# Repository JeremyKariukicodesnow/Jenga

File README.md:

# Jenga

**An open-source electronics workspace for people and external AI assistants.**

Jenga brings schematic editing, PCB layout, footprint and symbol libraries, and 3D assemblies into a Rust desktop application. Use the interface yourself, or connect an assistant through deterministic MCP, CLI and JSON tools. Jenga does not include a chat model, require an AI subscription, or make engineering decisions on its own.

Created and maintained by **Jeremy ([@JeremyKariukicodesnow](https://github.com/JeremyKariukicodesnow))**, with development assistance from **ChatGPT / OpenAI Codex**. This is an independent project, not an official KiCad or OpenAI product. The header is an AI-generated conceptual illustration, not an application screenshot.

## Status and downloads

**0.8.1 is early-access software for Windows x64.** It is suitable for evaluation and contributions; it is not a guarantee of production-ready PCB designs. Save backups, inspect exports and run native ERC/DRC before relying on a design. Electrical, thermal, mechanical and bench validation remain the designer's responsibility.

[Download latest Windows installer](https://jenga.sparkfield.co.ke/download/?start=1) · [Older versions / all releases](https://github.com/JeremyKariukicodesnow/Jenga/releases) · [0.8.1 early-access release](https://github.com/JeremyKariukicodesnow/Jenga/releases/tag/v0.8.1) · [User guide](docs/USER_GUIDE.md) · [PCB guide](docs/PCB_GUIDE.md) · [Validation evidence and limits](docs/RELEASE_080_VALIDATION.md)

**One permanent download link:** https://jenga.sparkfield.co.ke/download/?start=1 selects the highest published version, including early-access builds, and starts its EXE download. The public 0.8.1 early-access EXE is available now. [Older versions](https://github.com/JeremyKariukicodesnow/Jenga/releases) remain available separately; new releases never replace their original assets.

**Direct 0.8.1 downloads:**

- [Windows installer (.exe)](https://github.com/JeremyKariukicodesnow/Jenga/releases/download/v0.8.1/Jenga-windows-x64-Setup.exe)
- [Matching original source and Rust dependency source](https://github.com/JeremyKariukicodesnow/Jenga/releases/download/v0.8.1/Jenga-0.8.1-source.zip)
- [Checksums](https://github.com/JeremyKariukicodesnow/Jenga/releases/download/v0.8.1/SHA256SUMS)

Use the permanent download-page link for the newest published build, including previews. The version-specific links above keep the original 0.8.0 files. GitHub's `/latest` endpoint excludes prereleases; the [sharing/video guide](docs/SHARING_AND_VIDEOS.md) explains website buttons and future stable-release links. No demo video is uploaded yet.

The local build produces an installer, portable ZIP, corresponding Jenga/Rust dependency source ZIP and SHA-256 checksums. **The public [0.8.0 early-access release](https://github.com/JeremyKariukicodesnow/Jenga/releases/tag/v0.8.0) includes its installer, matching original source, checksums and a native-runtime notice/source supplement.** Published release artifacts are frozen; repository main can contain later dependency/CI/documentation changes. See [publication evidence and future release checks](docs/PUBLIC_RELEASE_CHECKLIST.md). Portable archives are available only where explicitly attached to a release. Do not use a source snapshot as an installer or treat an unlisted third-party download as an official build.

The complete Windows package includes symbols, footprints, 3D library data and the native KiCad backend; a separate KiCad installation is not required. This makes the offline package relatively large. Windows binaries are currently unsigned; there is no automatic online updater or established security audit.

## Why Jenga?

Jenga aims to make an electronics task useful in one workspace: draw the circuit, inspect connectivity, make a board, preview the assembly and export the result. For assistants, the same project has explicit tool targets, operation IDs and reviewable changes, reducing fragile screen-clicking and custom Python orchestration. People can still work directly in the desktop interface.

The stable connection bridge addresses a common interruption: after an app upgrade/downgrade, the assistant should recover its worker without the user repeatedly saying “reconnect.” Revision checks and previews protect human edits; they do not guarantee that an AI's electrical choices are correct.

It is a promising, useful prototype with substantial implemented workflows. **It is not perfect:** complex routing, advanced KiCad interoperability, engineering review and clean-machine coverage still need work. More generated tracks or an attractive 3D image do not prove a design is ready to manufacture.

## Requirements

| Requirement | Current position |
| --- | --- |
| Operating system | Windows x64 binary release; Windows 10/11 are the intended desktop targets. Broader clean-machine and driver coverage remains pending. No validated Linux/macOS binary releases yet. |
| Graphics | A working graphics driver for the OpenGL-based desktop renderer. VM/remote-desktop graphics compatibility is not comprehensively tested. |
| Disk | The complete extracted 0.8.0 payload is approximately **4.1 GB**; allow additional space for the download, installer staging, projects and exports. This is a measured payload size, not a universal minimum free-space guarantee. |
| Memory | Depends on board complexity and model size. No verified minimum-RAM figure or controlled performance benchmark is published yet. |
| KiCad | **Not required for the complete Jenga Windows package.** It includes the native backend and symbol, footprint and 3D libraries. A source-only checkout excludes those large binaries/assets and needs preparation steps. |
| AI | Optional. Manual editing requires no AI account or API key. Automation requires a local-capable assistant/client; its own provider/account and network requirements apply. |
| Internet | Not needed for local editing with the complete offline package. Needed for downloads, web asset discovery and any externally hosted assistant that requires it. |

Installing a binary does not require Rust or compiler tools; those are development requirements only. Download all of the portable package, rather than copying just Jenga.exe.

## What you can do

| Area | Available workflows |
| --- | --- |
| Schematics | Place and edit symbols; draw full wires, junctions and labels; manage independent drawings and hierarchical sheets; inspect connections and export drawings. |
| PCB | Create independent boards or optionally link a schematic; place footprints, route copper, manage layers/zones, inspect findings and export manufacturing data. |
| Libraries | Create/edit custom symbols and footprints; attach 3D models; import native assets into a project or personal library. |
| 3D | Inspect the assembly in a tab or separate window, adjust brightness/ambient light, export camera PNG/PDF views and supported CAD model formats. |
| Automation | MCP/CLI/JSON discovery, revision-guarded previews and commits, compact inspection, background calculations, progress/cancellation and durable operation receipts. |
| KiCad exchange | Open modern native projects/files; import projects or independent documents; exchange supported clipboard objects while preserving unknown fields in native files. |

Compatibility is incremental. Legacy `.sch`, every historic KiCad version and every advanced clipboard object are **not** supported. Unsupported clipboard objects are reported rather than silently discarded. Complete hierarchical projects use whole-project import. Jenga's approximate checks do not replace native DRC for complex rules. See the validation report for the precise test boundaries.

## Get started

When a verified binary release becomes available:

1. Download the versioned installer or portable ZIP and its `SHA256SUMS` from this repository's Releases page.
2. Check the downloaded hash, for example `Get-FileHash .\Jenga-0.8.0-windows-x64-Setup.exe -Algorithm SHA256`.
3. Run the installer, or extract the complete portable ZIP and launch `Jenga/Jenga.exe`.
4. Create/open a project, then add a schematic, PCB, or both. Linking a board to a schematic is optional.

For existing installations, Setup offers Upgrade, Repair or Downgrade and preserves project/personal data. Save work before maintenance. Keep a backup before downgrading a project made with newer features.

### Connect an assistant

Use **Connect Assistant** or the installed CLI:

```powershell
jenga-cli setup --client Codex --workspace "$env:USERPROFILE\Documents" --install --skill
```

Setup registers a stable `jenga-connect.exe` bridge outside the replaced application directory. Existing assistants need one restart to adopt it. Later worker upgrades/downgrades reconnect automatically without a new pasted configuration. Hosts that cannot refresh MCP tool lists may still need a restart. Interrupted edits are never replayed blindly: inspect the retained operation ID, then reopen the intended saved document if needed.

**Assistant setup:** built-in registration helpers cover Codex, Claude Code, Cursor and Antigravity. Other local MCP stdio clients can use the generated generic configuration; assistants with local command execution can use the CLI/JSON API. Browser-only chat does not automatically have access to local Jenga files. See [which assistants and setup recipes](docs/AI_ASSISTANTS.md).

The assistant supplies the engineering reasoning. The bundled skill covers exact part/datasheet evidence, power budgets, full visible wiring, readable labels, ground/antenna review and reusing appropriately licensed manufacturer/community assets. See [automation](docs/AUTOMATION.md) and the [skill](docs/assistant-skill/jenga-design/SKILL.md).

## Build from source

Install a current stable Rust toolchain (dependency MSRVs apply), Windows MSVC build tools and Git. The current desktop/release validation target is Windows x64.

```powershell
cargo test --workspace --locked
cargo run -p jenga-desktop
```

The repository includes font source and small fixtures, but deliberately excludes gigabytes of binary libraries, backend binaries, local settings, caches and personal projects. For a complete offline Windows package, obtain official KiCad 10 libraries/backend locally, then run:

```powershell
./scripts/prepare-libraries.ps1 -KiCadRoot 'C:\Program Files\KiCad\10.0'
./scripts/prepare-pcb-backend.ps1 -KiCadRoot 'C:\Program Files\KiCad\10.0'
./scripts/build-release.ps1
```

Inno Setup is needed to create Setup.exe. Audit redistribution notices/source availability before publishing a bundle. A dependency-vendored source archive accompanies binary releases; full offline library assets have separate provenance/licenses.

## Collaborate

Start with [CONTRIBUTING.md](CONTRIBUTING.md), [CODE_OF_CONDUCT.md](CODE_OF_CONDUCT.md) and [GOVERNANCE.md](GOVERNANCE.md). Fork, create a focused branch, add meaningful tests and open a pull request. Public visibility does not grant write or merge access. The maintainer controls upstream membership, merging, tags and releases; branch protection requires review and passing checks.

Report ordinary bugs with a minimal redistributable fixture. **Do not post credentials, personal projects or private security findings in public issues.** Follow [SECURITY.md](SECURITY.md) for vulnerabilities. AI-assisted contributions are welcome when reviewed and tested by the human contributor, with sources and limitations disclosed.

## Versioning and roadmap

`Cargo.toml` is the version source of truth. This release remains **0.8.0**. Tags use `v0.8.0`; release labels distinguish drafts, early-access prereleases and stable releases without silently changing the application's version.

Before 1.0, minor versions may change preview APIs. Existing projects must remain protected by explicit migrations and backups. Patches contain fixes; minors add features; a future 1.0 requires a documented compatibility/support commitment. Never replace published release assets silently. See [CHANGELOG.md](CHANGELOG.md) and [release policy](docs/RELEASING.md).

Next priorities are broader KiCad interoperability fixtures, clean-machine validation, independent engineering review, code signing, third-party distribution completeness and measured performance benchmarks.

## License and acknowledgements

Jenga's code is licensed under **GPL-3.0-or-later**, subject to the separately identified third-party material. Commercial use is allowed under the applicable licenses; this is not a proprietary license or an exclusive ownership claim over upstream work.

Thank you to the **KiCad developers, library contributors, Vladimir Uryvaev and NewStroke contributors**, and the maintainers of Rust dependencies and native runtime dependencies. The NewStroke source is included with its notices; KiCad libraries and backend have their own distribution obligations. See [THIRD_PARTY_NOTICES.md](THIRD_PARTY_NOTICES.md), [AUTHORS.md](AUTHORS.md) and [LICENSE](LICENSE).

No warranty is provided. Jenga is not affiliated with or endorsed by KiCad or OpenAI. Attribution, tests and a license do not substitute for a security audit, license compliance review or hardware validation.

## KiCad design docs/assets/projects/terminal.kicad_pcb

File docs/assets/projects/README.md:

# Project showcase exports

These PNGs are unmodified exports copied from Jeremy's local 555 Pulse Generator, Maize Factory, and Access Terminal S3 projects for the public Jenga showcase. They show design artifacts, not fabricated or certified hardware. The terminal remains subject to engineering review, as described on the website. The Maize Factory project is represented by its power and control schematics only.

The GLB files are actual exported 3D assemblies, not turntable videos. Native schematic and PCB files are offered for inspection. Native boards can reference project-specific external models or libraries; the self-contained GLB is the portable visual assembly. Downloads are development examples, not manufacturing-approved designs.

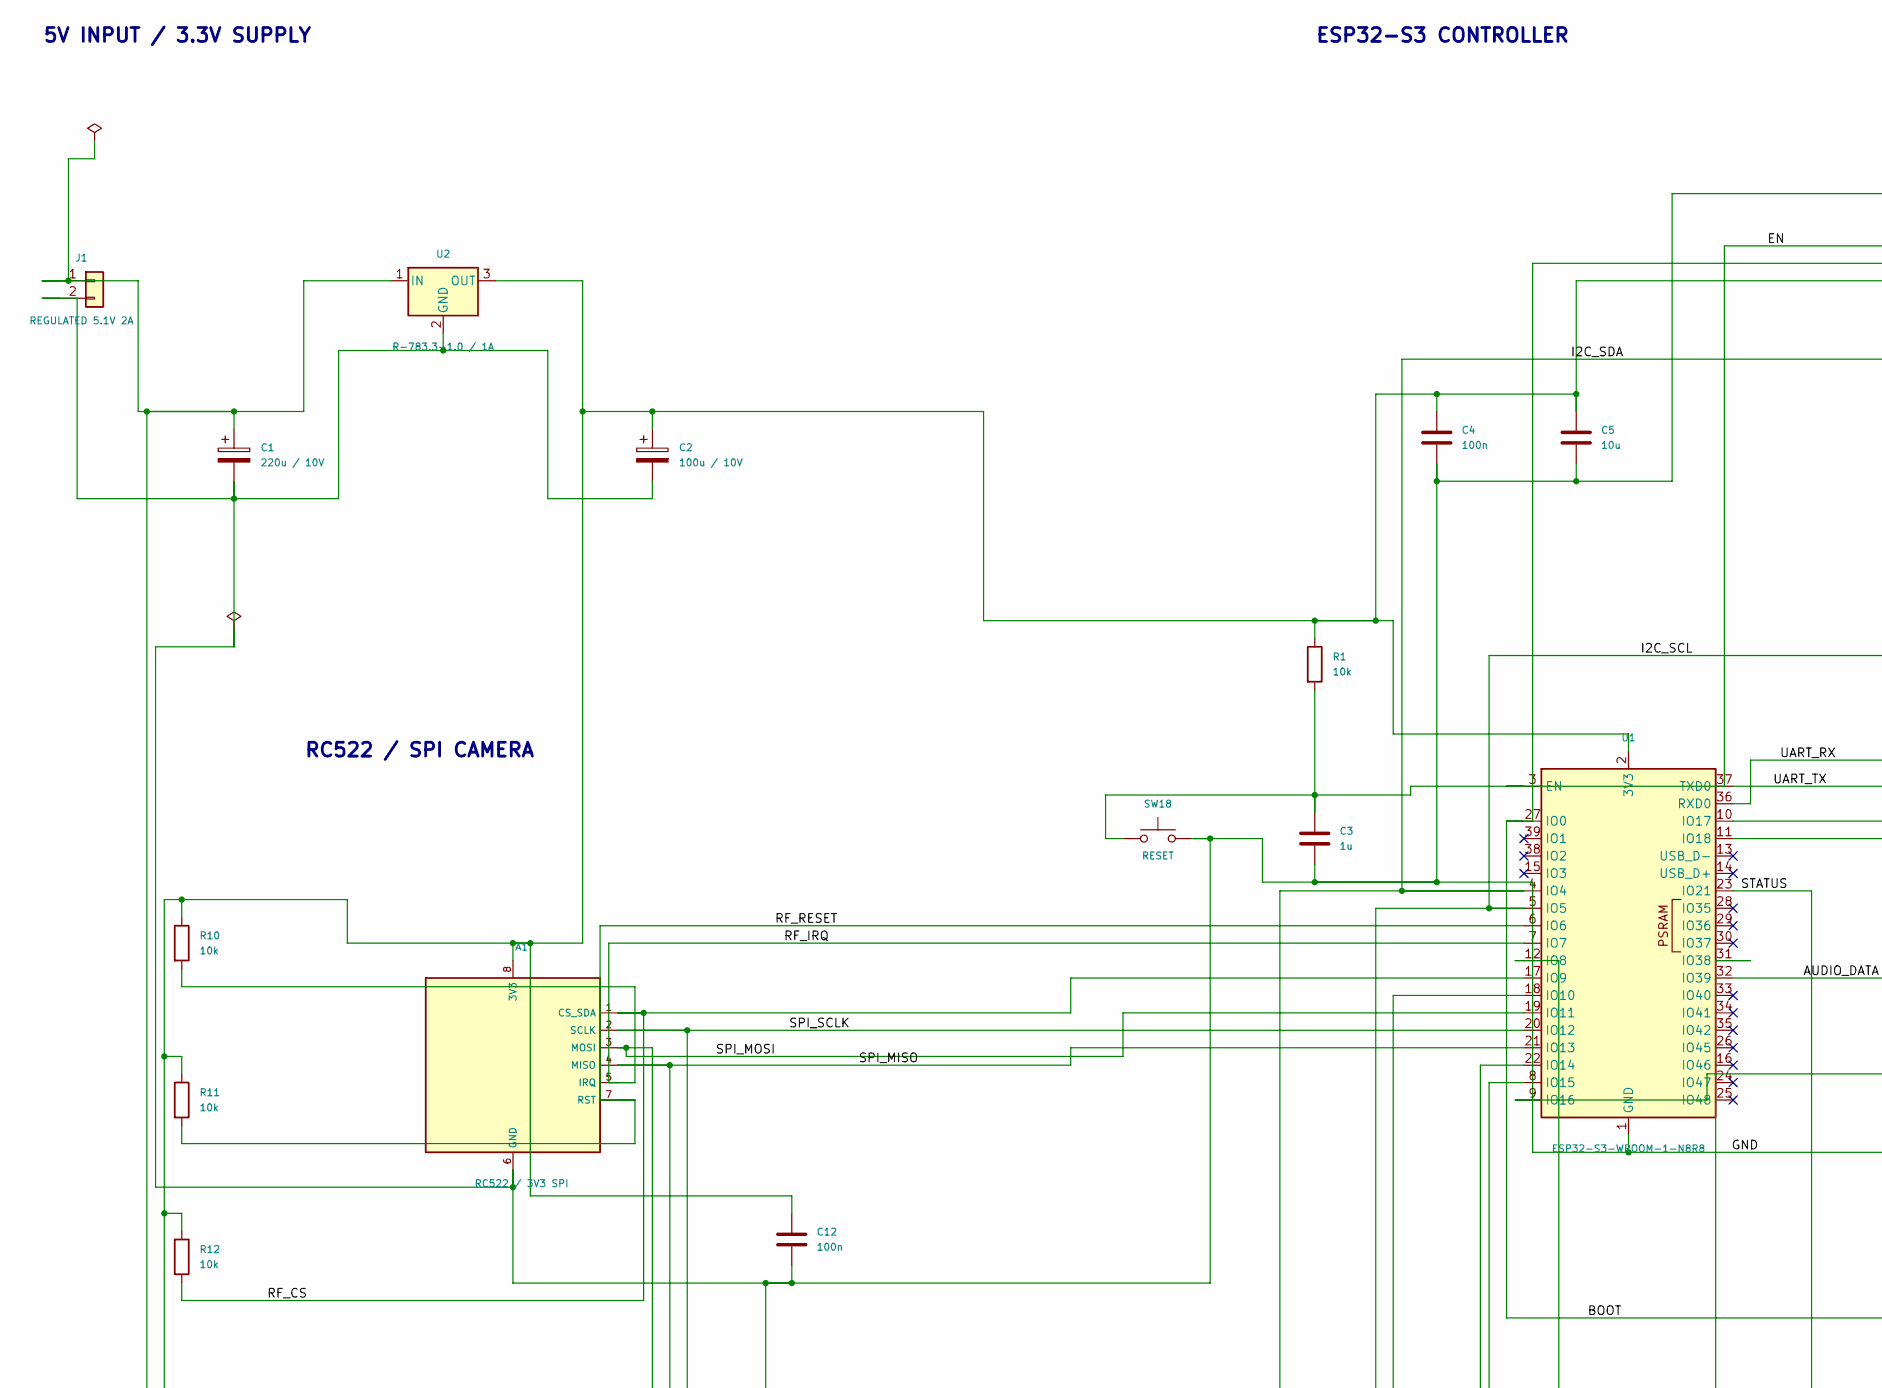
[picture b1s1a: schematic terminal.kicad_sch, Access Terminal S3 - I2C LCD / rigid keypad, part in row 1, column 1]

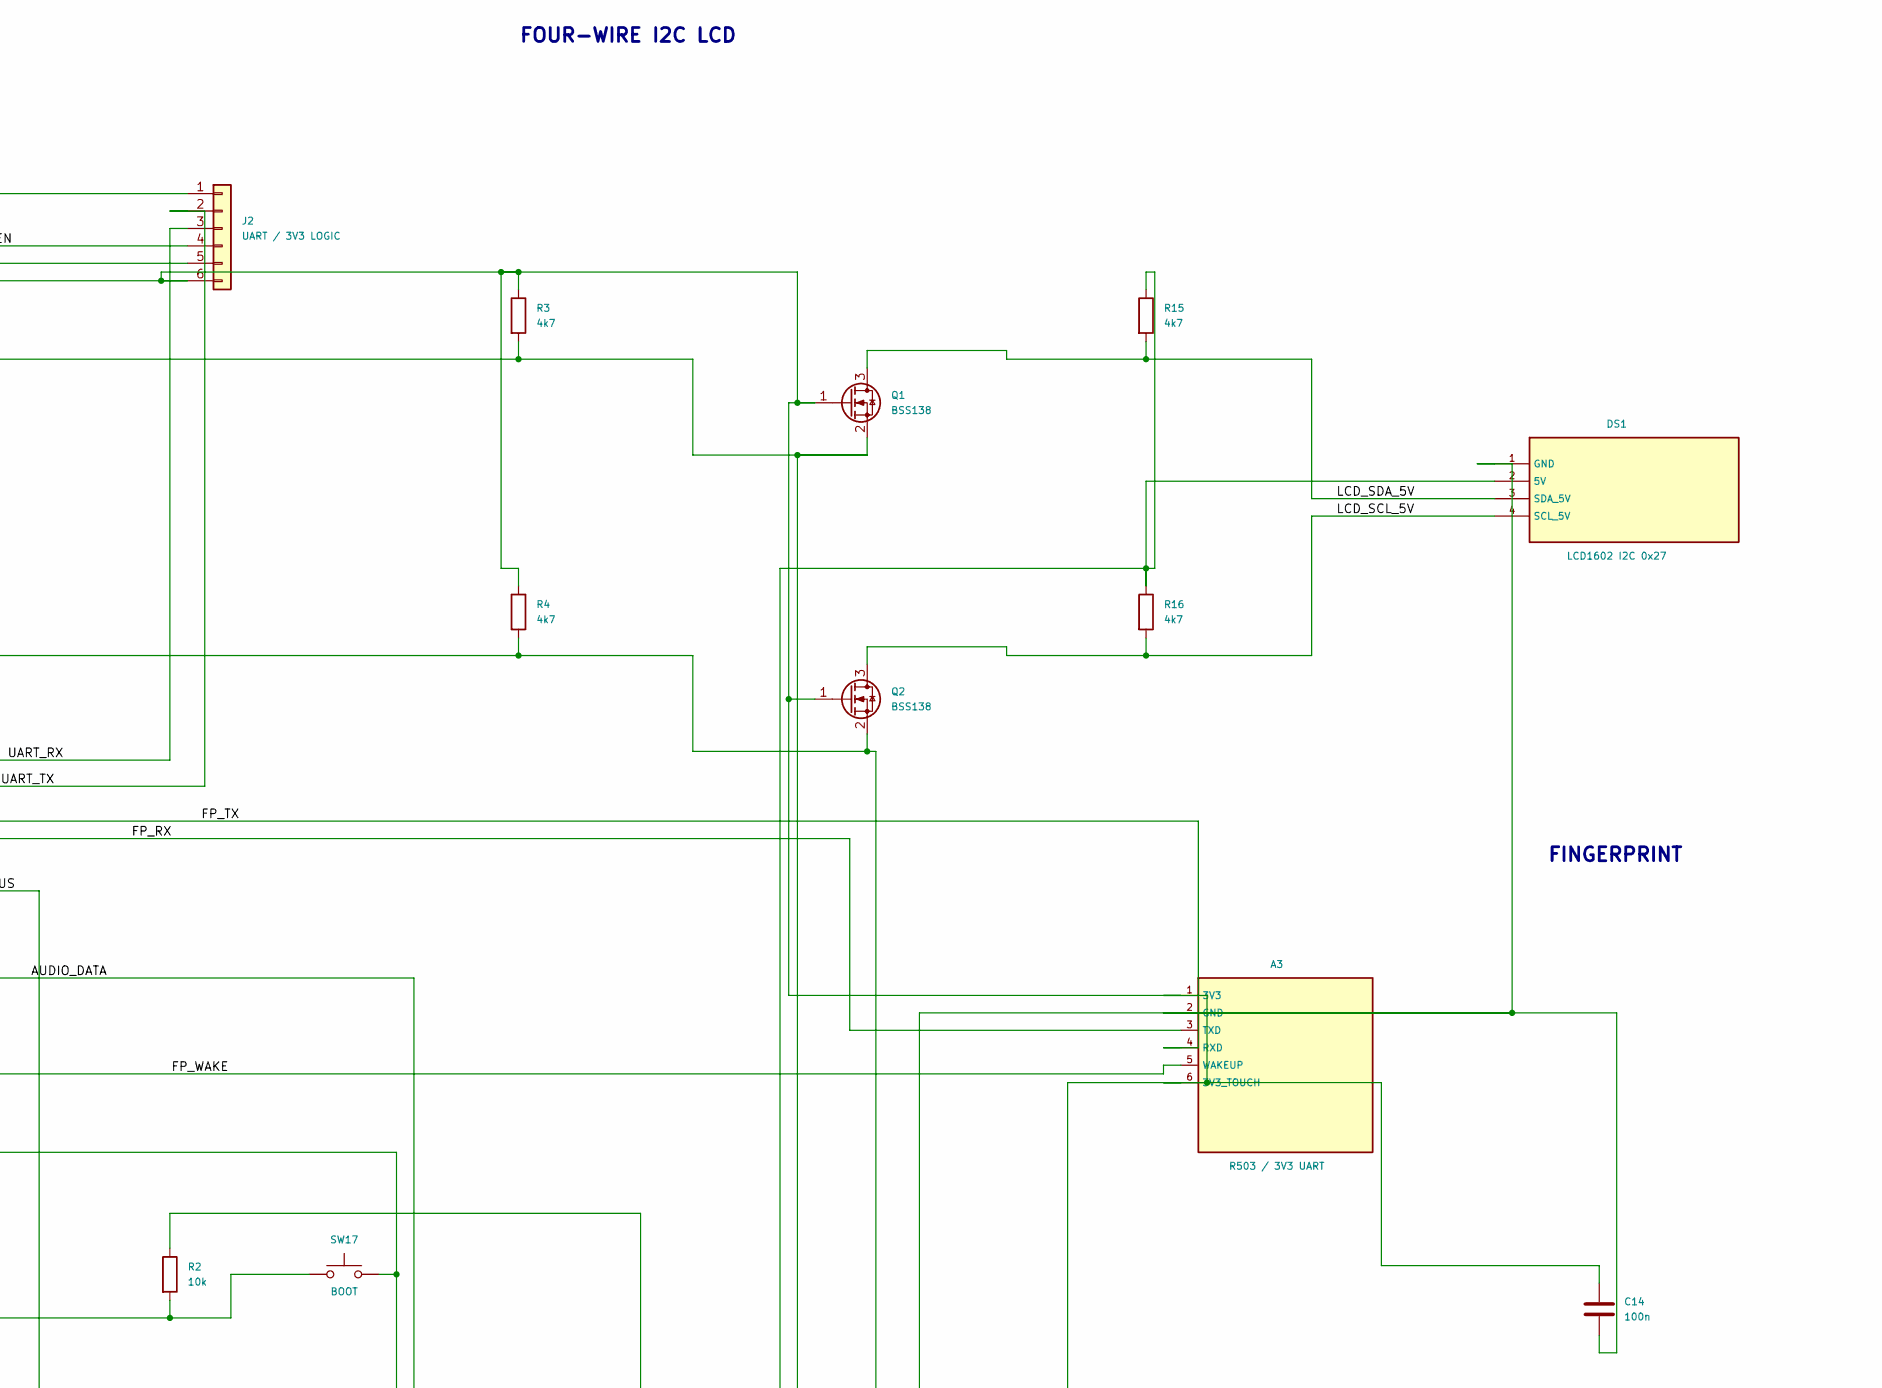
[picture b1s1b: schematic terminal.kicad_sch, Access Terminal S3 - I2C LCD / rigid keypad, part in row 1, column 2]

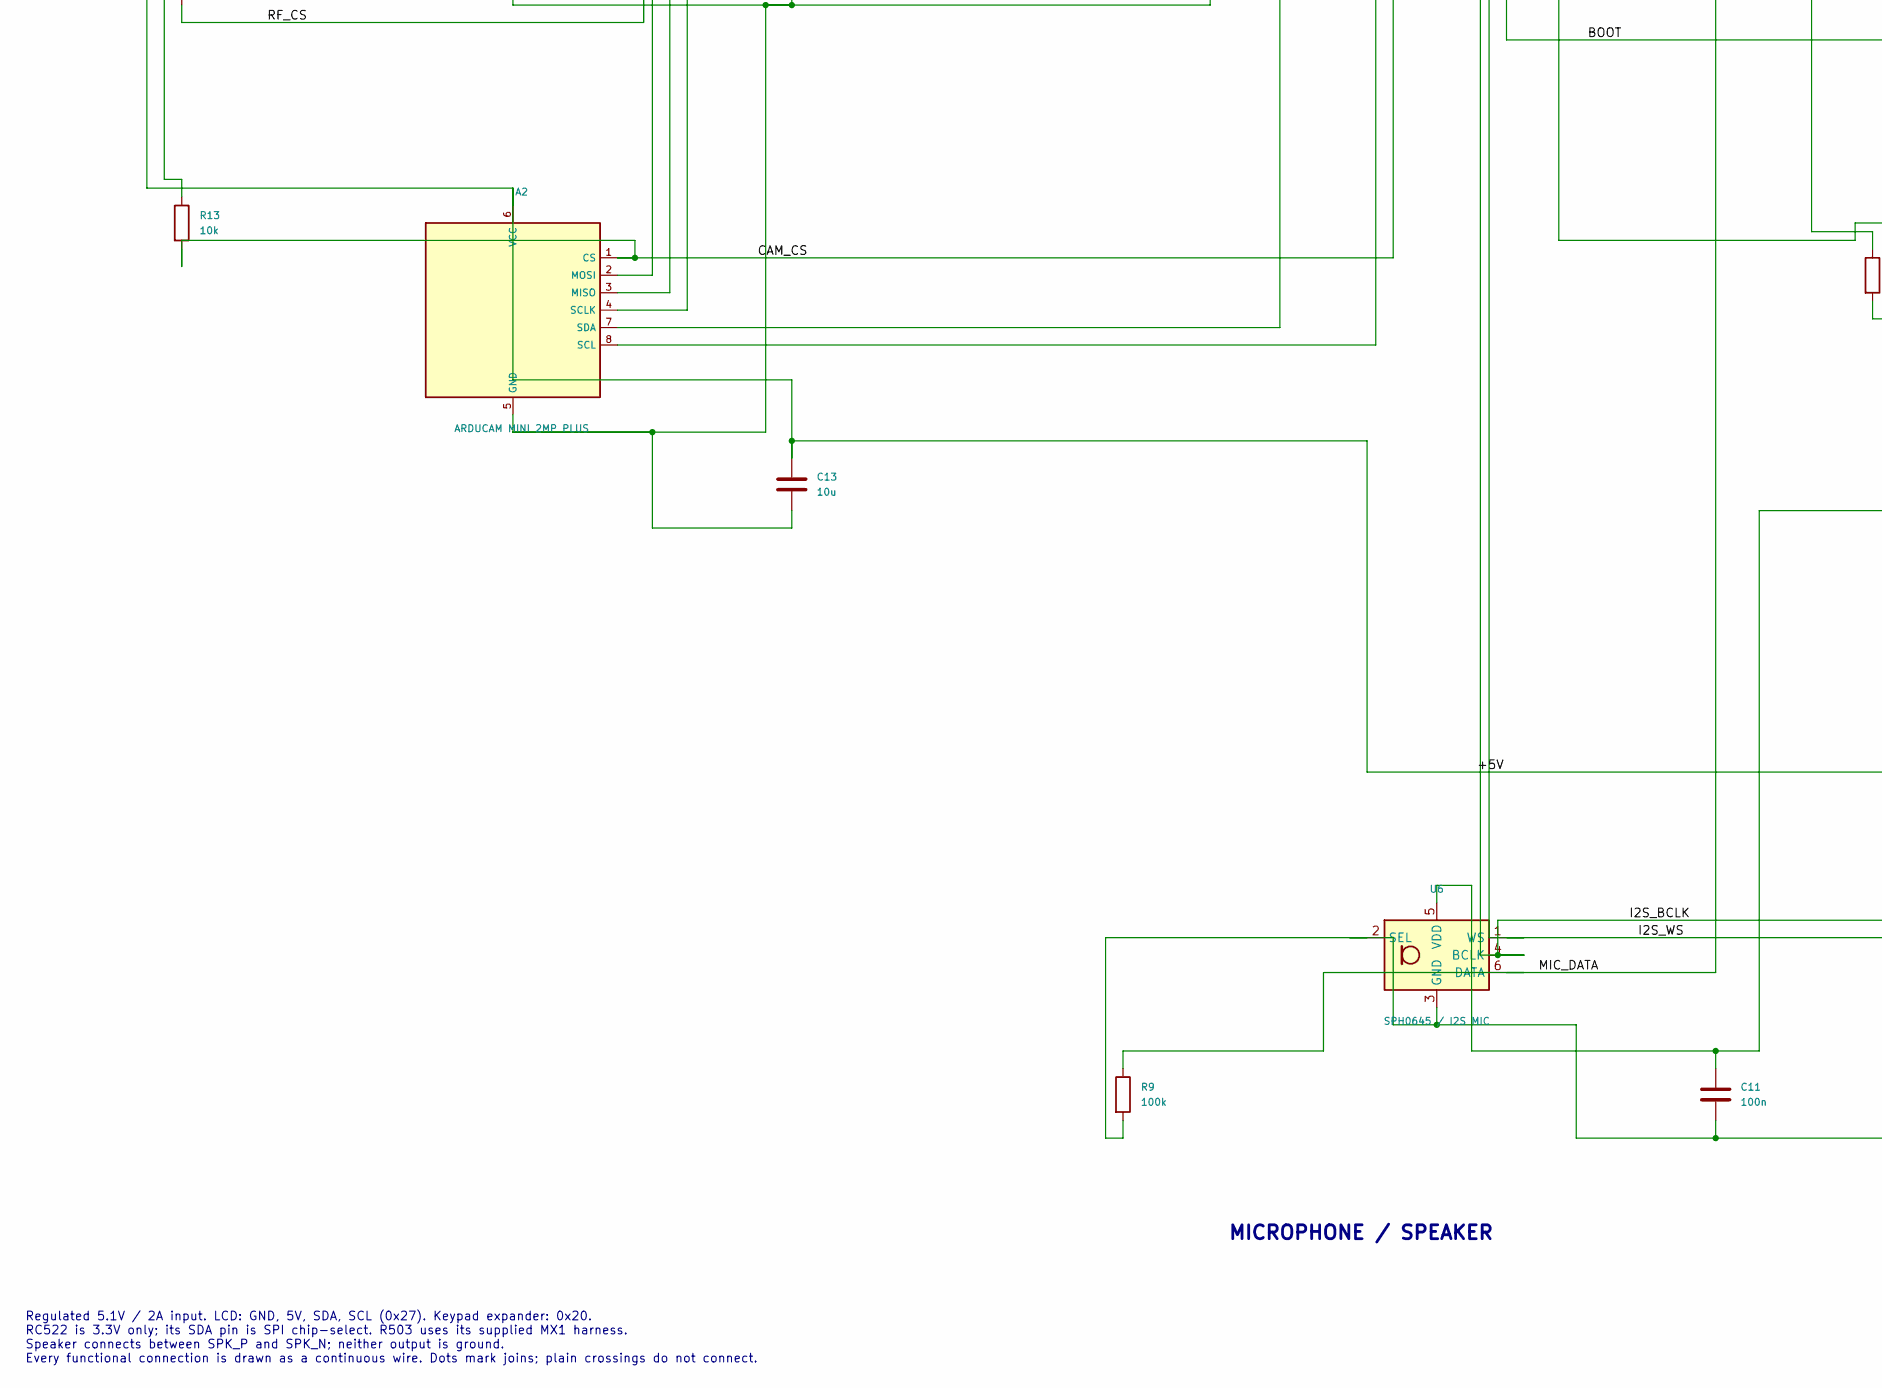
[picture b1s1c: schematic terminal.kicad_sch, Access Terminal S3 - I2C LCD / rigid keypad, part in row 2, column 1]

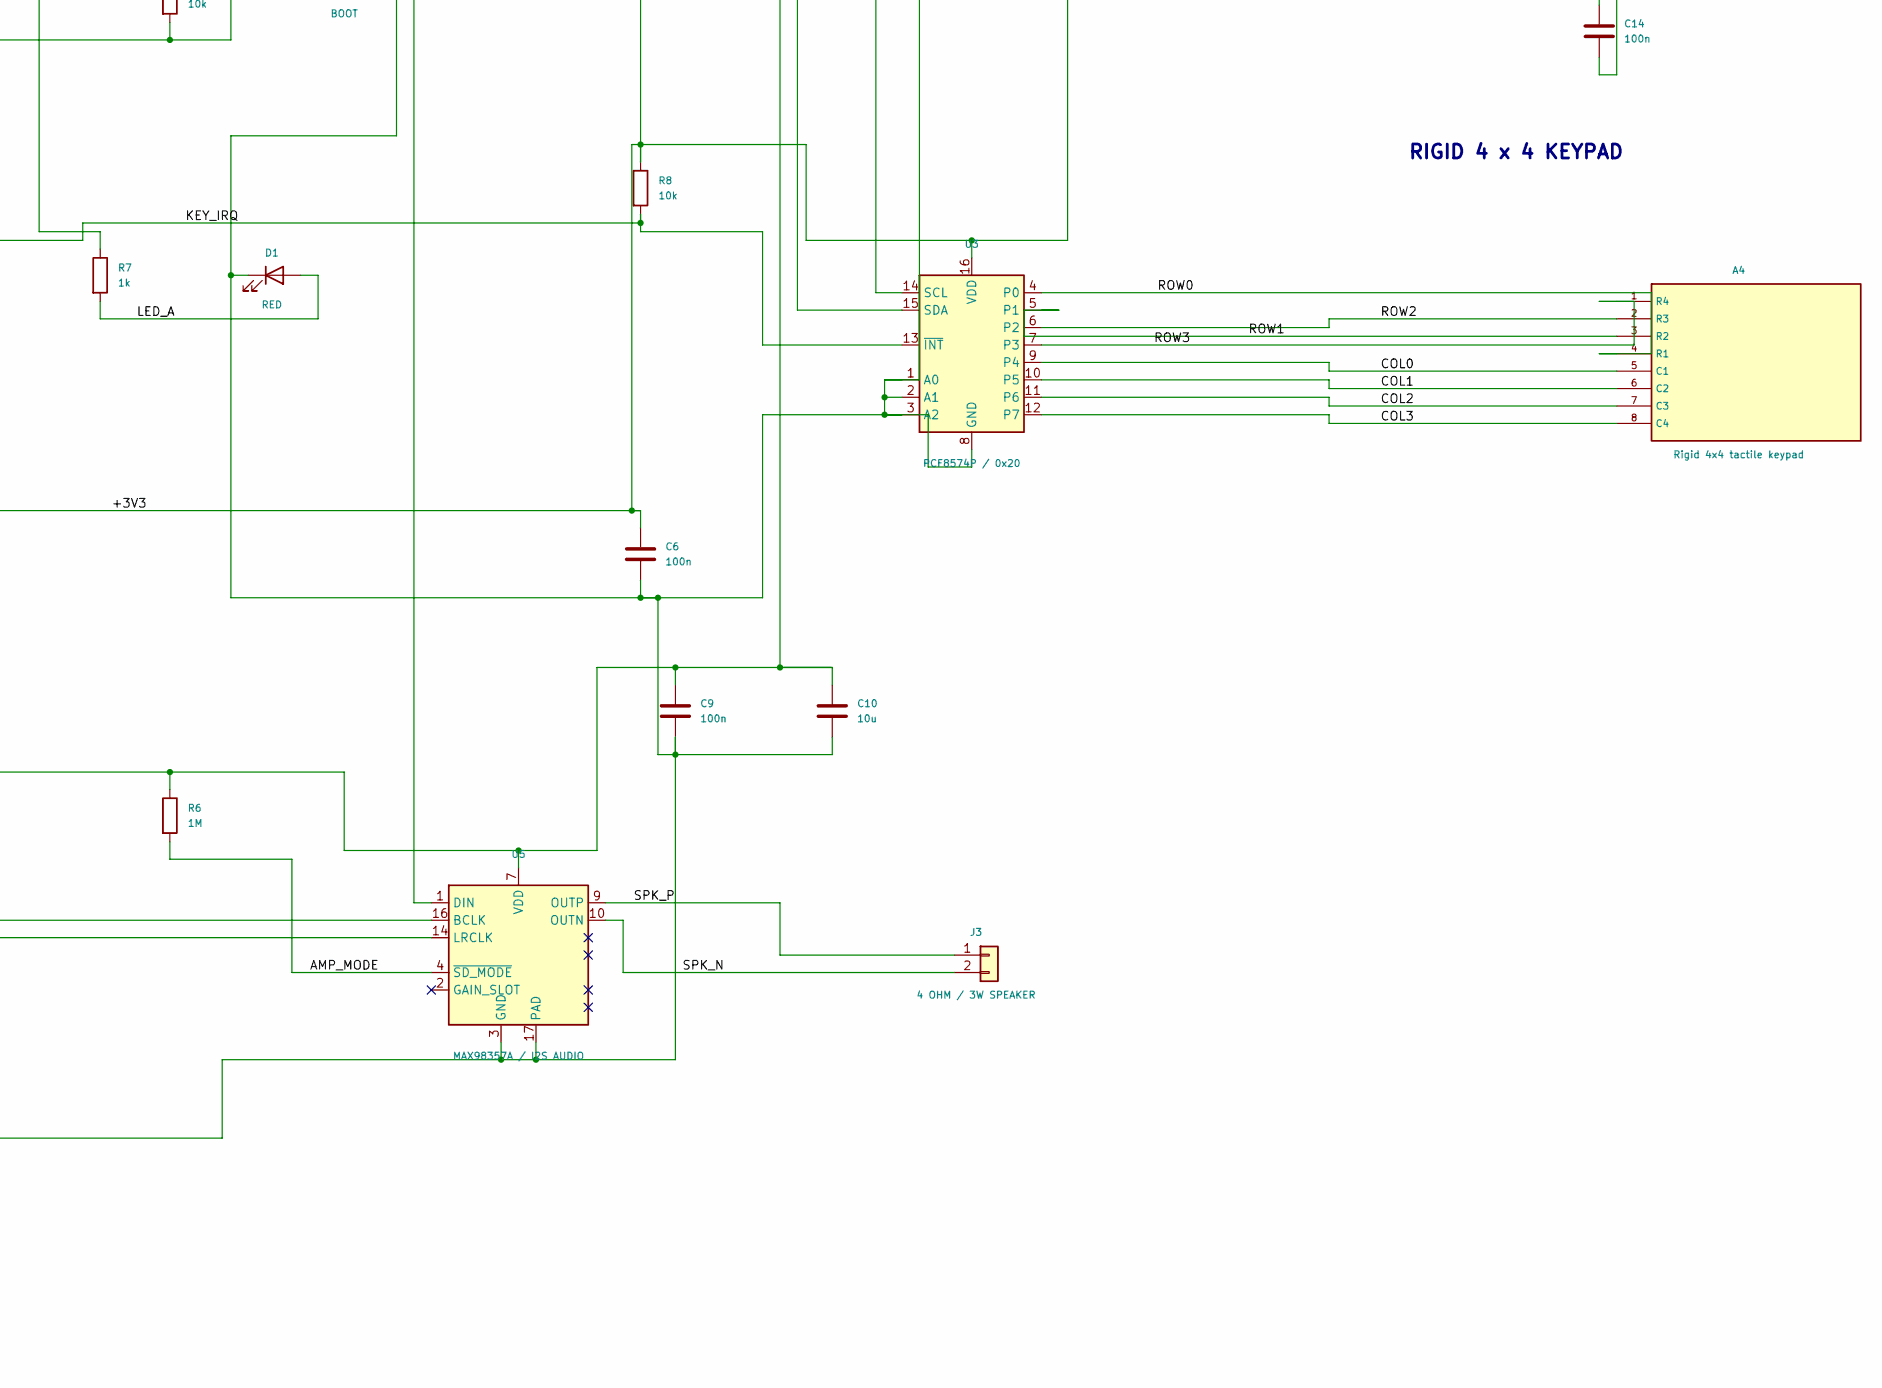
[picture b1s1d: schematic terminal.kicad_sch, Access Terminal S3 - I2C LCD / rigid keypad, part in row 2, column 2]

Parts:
A1: RC522 / 3V3 SPI; RC522_Module
A2: ARDUCAM MINI 2MP PLUS; ArducamMini_Module
A3: R503 / 3V3 UART; R503_Cable
A4: Rigid 4x4 tactile keypad; Keypad4x4_Rigid
C1: 220u / 10V; CP220
C2: 100u / 10V; CP100
C3: 1u; C0805
C4, C6, C9, C11, C12, C14: 100n; C0805
C5, C10, C13: 10u; C0805
D1: RED; LED3
DS1: LCD1602 I2C 0x27; LCD1602_I2C
J1: REGULATED 5.1V 2A; Power5V
J2: UART / 3V3 LOGIC; Program6
J3: 4 OHM / 3W SPEAKER; Speaker_Panel
Q1, Q2: BSS138; SOT23
R1, R2, R8, R10, R11, R12, R13: 10k; R0805
R3, R4, R15, R16: 4k7; R0805
R6: 1M; R0805
R7: 1k; R0805
R9: 100k; R0805
SW17: BOOT; Key6mm
SW18: RESET; Key6mm
U1: ESP32-S3-WROOM-1-N8R8; ESP32S3
U2: R-783.3-1.0 / 1A; RECOM_R7833_1A
U3: PCF8574P / 0x20; DIP16
U5: MAX98357A / I2S AUDIO; MAX98357A
U6: SPH0645 / I2S MIC; Microphone

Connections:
+3V3: A1.8 (3V3), A3.1 (3V3), A3.6 (3V3_TOUCH), C2.1, C4.1, C5.1, C6.1, C11.1, C12.1, C14.1, J2.6, Q1.1 (G), Q2.1 (G), R1.1, R2.1, R3.1, R4.1, R8.1, R10.1, R11.1, R12.1, R13.1, U1.2 (3V3), U2.3 (OUT), U3.16 (VDD), U6.5 (VDD)
+5V: A2.6 (VCC), C1.1, C9.1, C10.1, C13.1, DS1.2 (5V), J1.1, R6.1, R15.1, R16.1, U2.1 (IN), U5.7 (VDD), U5.8 (VDD)
AMP_MODE: R6.2, U5.4 (~SD_MODE)
AUDIO_DATA: U1.32 (IO39), U5.1 (DIN)
BOOT: J2.5, R2.2, SW17.1, U1.27 (IO0)
CAM_CS: A2.1 (CS), R13.2, U1.18 (IO10)
COL0: A4.5 (C1), U3.9 (P4)
COL1: A4.6 (C2), U3.10 (P5)
COL2: A4.7 (C3), U3.11 (P6)
COL3: A4.8 (C4), U3.12 (P7)
EN: C3.1, J2.4, R1.2, SW18.1, U1.3 (EN)
FP_RX: A3.3 (TXD), U1.11 (IO18)
FP_TX: A3.4 (RXD), U1.10 (IO17)
FP_WAKE: A3.5 (WAKEUP), U1.9 (IO16)
GND: A1.6 (GND), A2.5 (GND), A3.2 (GND), C1.2, C2.2, C3.2, C4.2, C5.2, C6.2, C9.2, C10.2, C11.2, C12.2, C13.2, C14.2, D1.1 (K), DS1.1 (GND), J1.2, J2.1, R9.2, SW17.2, SW18.2, U1.1 (GND), U1.40 (GND), U1.41 (GND), U2.2 (GND), U3.1 (A0), U3.2 (A1), U3.3 (A2), U3.8 (GND), U5.3 (GND), U5.11 (GND), U5.15 (GND), U5.17 (PAD), U6.2 (SEL), U6.3 (GND)
I2C_SCL: A2.8 (SCL), Q2.2 (S), R4.2, U1.5 (IO5), U3.14 (SCL)
I2C_SDA: A2.7 (SDA), Q1.2 (S), R3.2, U1.4 (IO4), U3.15 (SDA)
I2S_BCLK: U1.22 (IO14), U5.16 (BCLK), U6.4 (BCLK)
I2S_WS: U1.8 (IO15), U5.14 (LRCLK), U6.1 (WS)
KEY_IRQ: R8.2, U1.12 (IO8), U3.13 (~INT)
LCD_SCL_5V: DS1.4 (SCL_5V), Q2.3 (D), R16.2
LCD_SDA_5V: DS1.3 (SDA_5V), Q1.3 (D), R15.2
LED_A: D1.2 (A), R7.2
MIC_DATA: R9.1, U1.31 (IO38), U6.6 (DATA)
Net-U1-1: U1.13 (USB_D-)
Net-U1-2: U1.14 (USB_D+)
Net-U1-3: U1.15 (IO3)
Net-U1-4: U1.16 (IO46)
Net-U1-5: U1.24 (IO47)
Net-U1-6: U1.25 (IO48)
Net-U1-7: U1.26 (IO45)
Net-U1-8: U1.28 (IO35)
Net-U1-9: U1.29 (IO36)
Net-U1-10: U1.30 (IO37)
Net-U1-11: U1.33 (IO40)
Net-U1-12: U1.34 (IO41)
Net-U1-13: U1.35 (IO42)
Net-U1-14: U1.38 (IO2)
Net-U1-15: U1.39 (IO1)
Net-U5-43: U5.2 (GAIN_SLOT)
Net-U5-44: U5.5 (NC)
Net-U5-45: U5.6 (NC)
Net-U5-46: U5.12 (NC)
Net-U5-47: U5.13 (NC)
RF_CS: A1.1 (CS_SDA), R12.2, U1.17 (IO9)
RF_IRQ: A1.5 (IRQ), R10.2, U1.7 (IO7)
RF_RESET: A1.7 (RST), R11.2, U1.6 (IO6)
ROW0: A4.4 (R1), U3.4 (P0)
ROW1: A4.3 (R2), U3.5 (P1)
ROW2: A4.2 (R3), U3.6 (P2)
ROW3: A4.1 (R4), U3.7 (P3)
SPI_MISO: A1.4 (MISO), A2.3 (MISO), U1.21 (IO13)
SPI_MOSI: A1.3 (MOSI), A2.2 (MOSI), U1.19 (IO11)
SPI_SCLK: A1.2 (SCLK), A2.4 (SCLK), U1.20 (IO12)
SPK_N: J3.2, U5.10 (OUTN)
SPK_P: J3.1, U5.9 (OUTP)
STATUS: R7.1, U1.23 (IO21)
UART_RX: J2.3, U1.36 (RXD0)
UART_TX: J2.2, U1.37 (TXD0)

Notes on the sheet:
5V INPUT / 3.3V SUPPLY
ESP32-S3 CONTROLLER
FOUR-WIRE I2C LCD
RC522 / SPI CAMERA
FINGERPRINT
RIGID 4 x 4 KEYPAD
MICROPHONE / SPEAKER
Regulated 5.1V / 2A input. LCD: GND, 5V, SDA, SCL (0x27). Keypad expander: 0x20. RC522 is 3.3V only; its SDA pin is SPI chip-select. R503 uses its supplied MX1 harness. Speaker connects between SPK_P and SPK_N; neither output is ground. Every functional connection is drawn as a continuous wire. Dot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

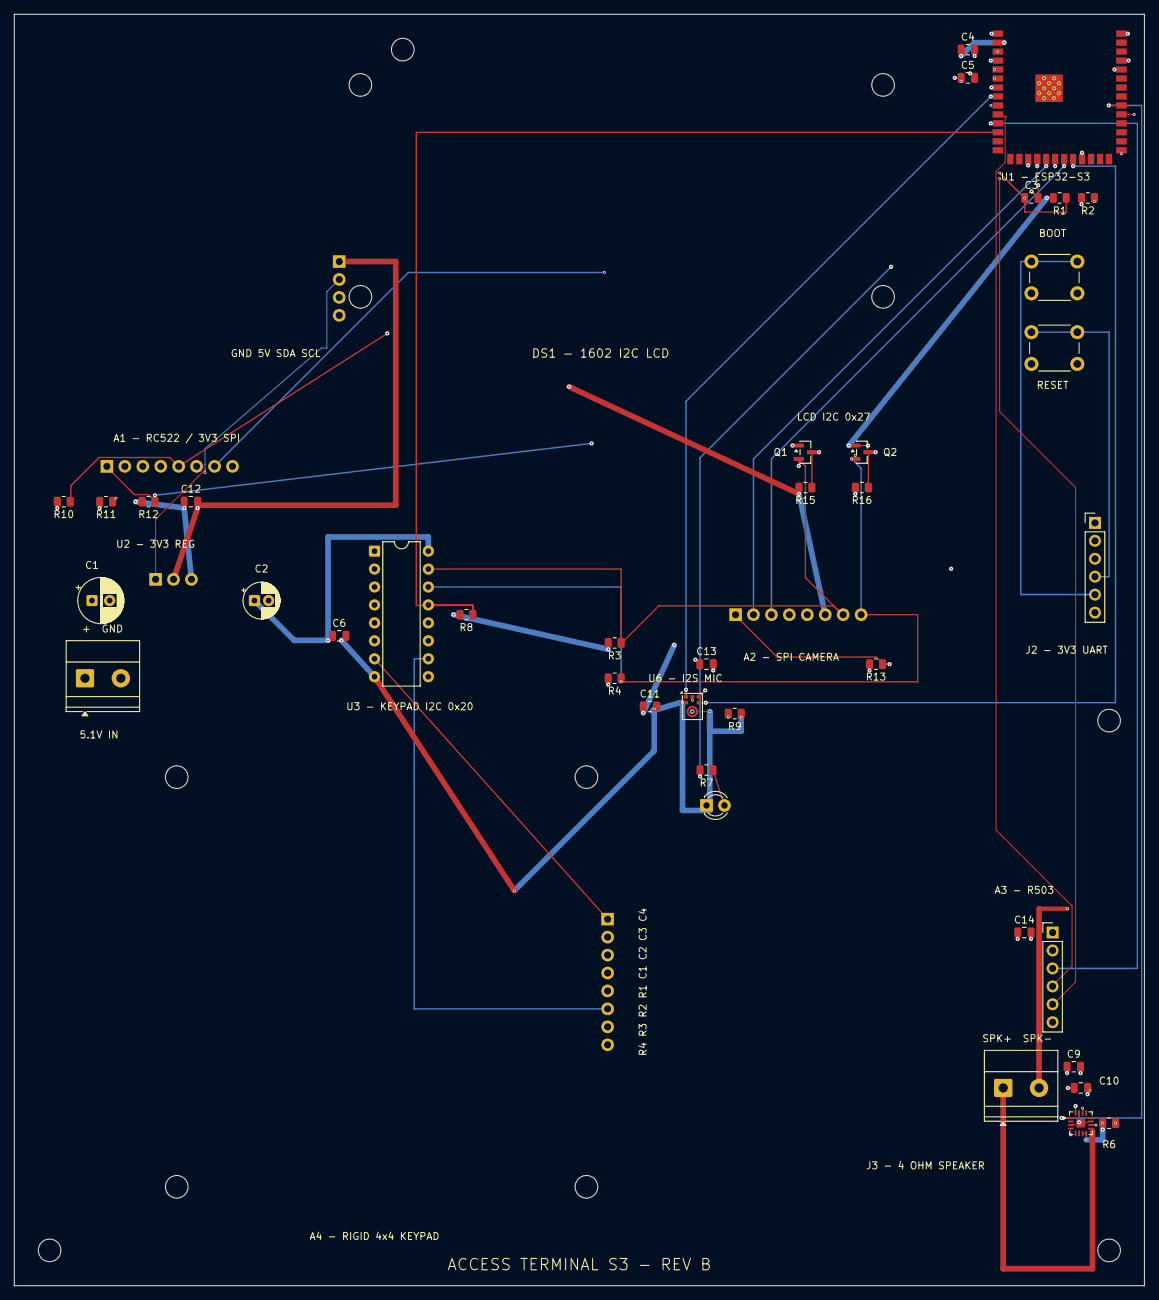
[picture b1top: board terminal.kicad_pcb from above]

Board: 4 copper layers, 160.0 x 180.0 mm, 48 parts (0 on the bottom side), 39 nets.

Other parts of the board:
H1, H2, H3, H4: M3 standoff; M3

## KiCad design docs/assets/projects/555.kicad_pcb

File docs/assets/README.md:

# README artwork

`jenga-hero.png` was generated for Jeremy's Jenga repository using the built-in OpenAI image generation tool, with ChatGPT/Codex assistance. It is conceptual electronics artwork, not a screenshot, functional circuit, certified PCB or KiCad/OpenAI endorsement. No third-party logo or stock image was supplied as an input. Do not use it as electrical design evidence.

Prompt: Create a polished wide 16:9 editorial hero illustration for the GitHub README of Jenga, an independent open source electronic CAD application. A refined light ivory technical drafting sheet background, a precise dark ink schematic circuit at left flowing into a realistic forest-green printed circuit board with copper traces, ICs, resistors and pin headers in isometric view at right. Restrained red accent dots and fine blueprint grid. Sophisticated clean engineering visual, generous negative space, tactile realistic PCB materials, sharp legible composition, no fake app screenshots or fabricated UI. Put only the exact word JENGA in large dark dot-matrix lettering at upper left and the small exact line Schematics · PCB · 3D below it. No KiCad logo, no other logos, no certification marks, no claims of production readiness. This is a conceptual illustration, not a screenshot.

The download page reuses the owner-supplied `resources/branding/jenga.png` and `.ico` byte-for-byte as `jenga-logo.png` and `jenga.ico`. `jenga-wordmark.svg` reproduces Jenga’s original 5×7 dot glyphs from `crates/jenga-desktop/src/design.rs`; it does not use a proprietary font. Circuit decoration and animation are native SVG/CSS.

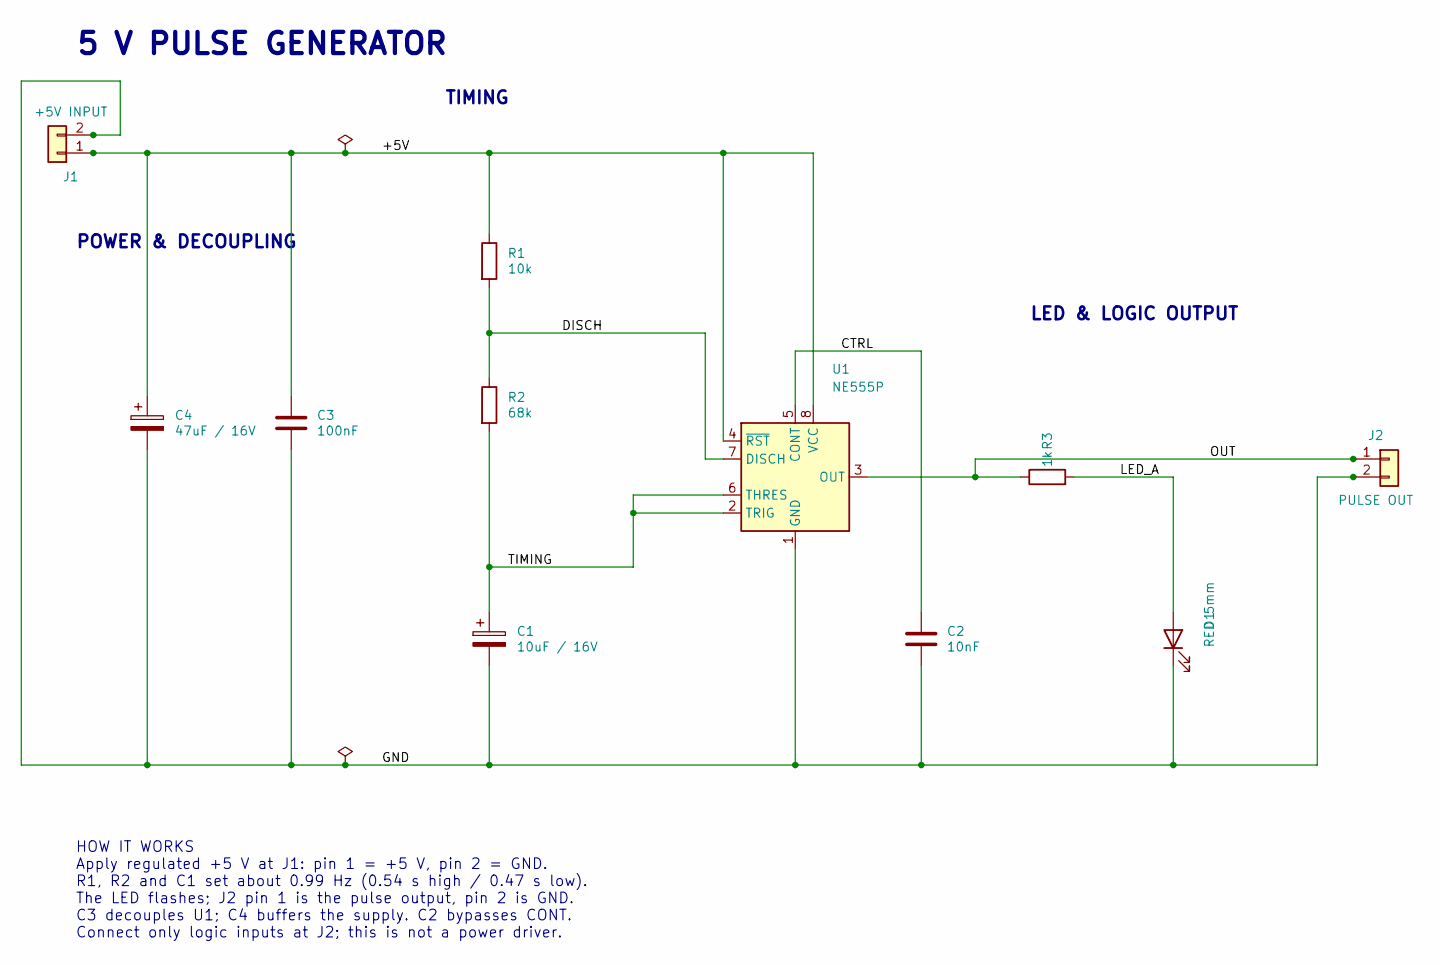
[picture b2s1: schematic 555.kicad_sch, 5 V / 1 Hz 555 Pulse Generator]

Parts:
C1: 10uF / 16V; CP_Radial_D5.0mm_P2.00mm
C2: 10nF; C_Disc_D5.0mm_W2.5mm_P5.00mm
C3: 100nF; C_Disc_D5.0mm_W2.5mm_P5.00mm
C4: 47uF / 16V; CP_Radial_D5.0mm_P2.00mm
D1: RED 5mm; LED_D5.0mm
J1: +5V INPUT; PinHeader_1x02_P2.54mm_Vertical
J2: PULSE OUT; PinHeader_1x02_P2.54mm_Vertical
R1: 10k; R_Axial_DIN0207_L6.3mm_D2.5mm_P7.62mm_Horizontal
R2: 68k; R_Axial_DIN0207_L6.3mm_D2.5mm_P7.62mm_Horizontal
R3: 1k; R_Axial_DIN0207_L6.3mm_D2.5mm_P7.62mm_Horizontal
U1: NE555P; DIP-8_W7.62mm

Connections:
+5V: C3.1, C4.1, J1.1, R1.1, U1.4 (~RST), U1.8 (VCC)
CTRL: C2.1, U1.5 (CONT)
DISCH: R1.2, R2.1, U1.7 (DISCH)
GND: C1.2, C2.2, C3.2, C4.2, D1.1 (K), J1.2, J2.2, U1.1 (GND)
LED_A: D1.2 (A), R3.2
OUT: J2.1, R3.1, U1.3 (OUT)
TIMING: C1.1, R2.2, U1.2 (TRIG), U1.6 (THRES)

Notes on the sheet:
5 V PULSE GENERATOR
POWER & DECOUPLING
TIMING
LED & LOGIC OUTPUT
HOW IT WORKS Apply regulated +5 V at J1: pin 1 = +5 V, pin 2 = GND. R1, R2 and C1 set about 0.99 Hz (0.54 s high / 0.47 s low). The LED flashes; J2 pin 1 is the pulse output, pin 2 is GND. C3 decouples U1; C4 buffers the supply. C2 bypasses CONT. Connect only logic inputs at J2; this is not a power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

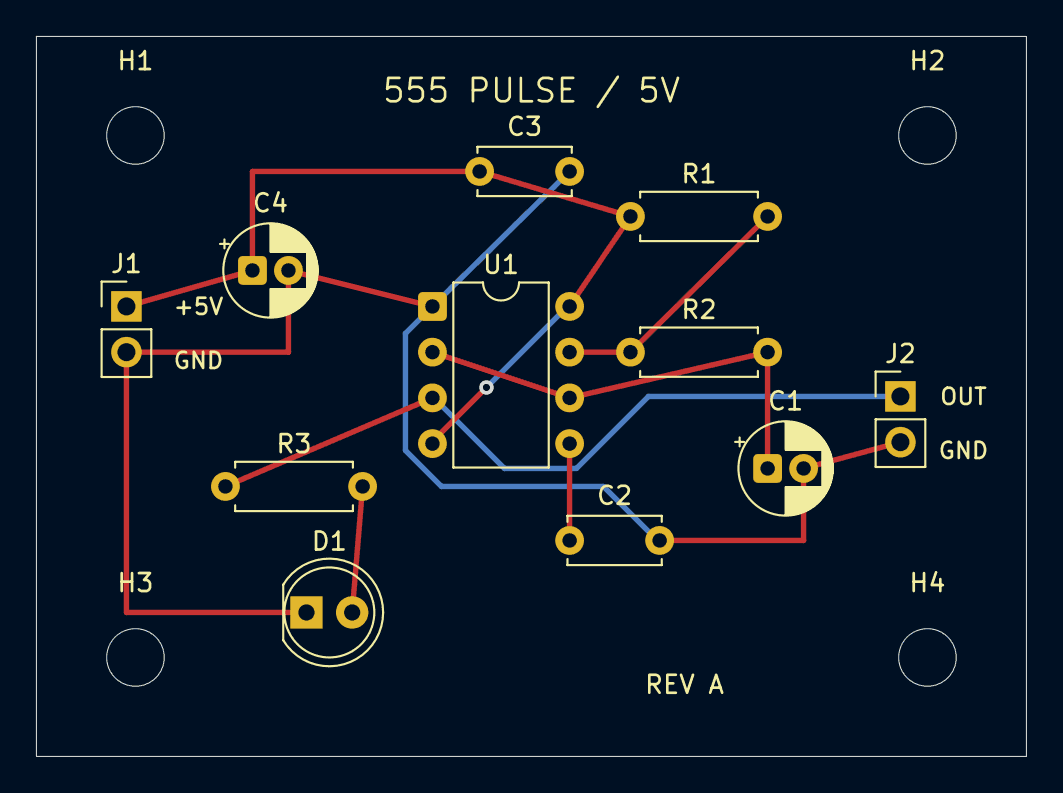
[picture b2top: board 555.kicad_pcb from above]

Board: 2 copper layers, 55.0 x 40.0 mm, 15 parts (0 on the bottom side), 7 nets.

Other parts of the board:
H1, H2, H3, H4: M3; MountingHole_3.2mm_M3

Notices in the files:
README.md:
License: GPL-3.0-or-later
